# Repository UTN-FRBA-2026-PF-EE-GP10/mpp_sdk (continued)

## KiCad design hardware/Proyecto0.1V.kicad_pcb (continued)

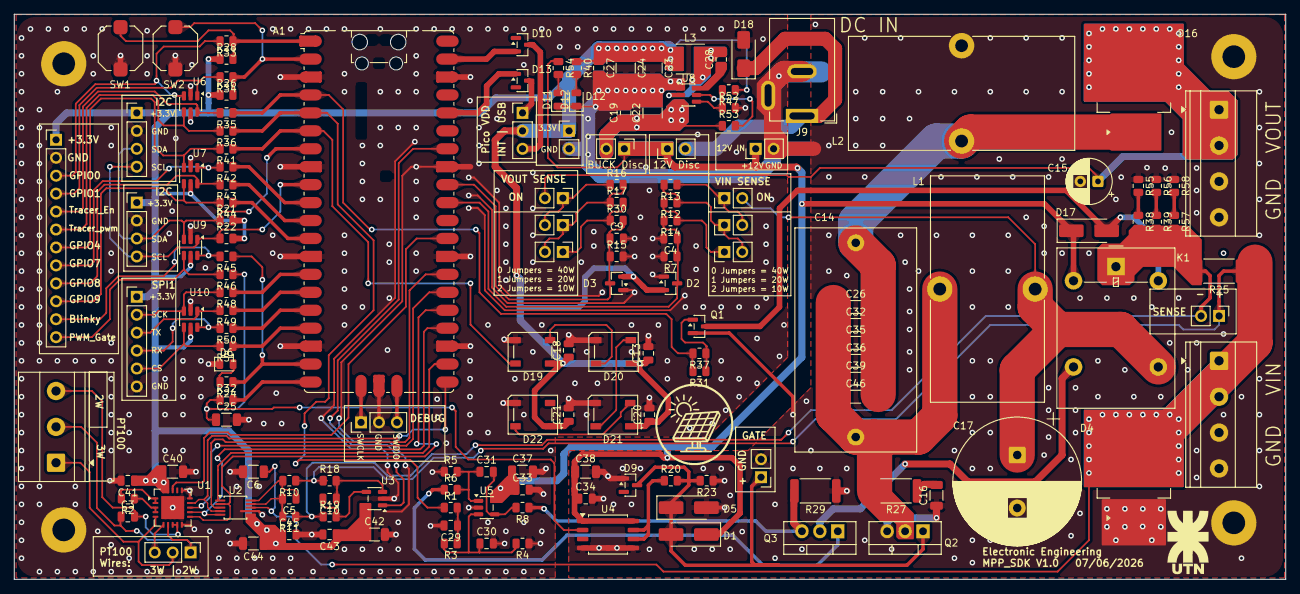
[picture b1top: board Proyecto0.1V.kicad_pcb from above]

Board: 2 copper layers, 180.0 x 80.0 mm, 166 parts (1 on the bottom side), 102 nets.

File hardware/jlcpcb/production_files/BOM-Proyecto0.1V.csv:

Comment,Designator,Footprint,LCSC,Quantity
1TS009A-1800-5000-CT,"SW1,SW2",SW_Push_1TS009xxxx-xxxx-xxxx_6x6x5mm,C319409,2
AP62250WU-7,U8,TSOT-23-6,C5184228,1
BAT54SLT1G,"D10,D13,D2,D3",SOT-23,C19726,4
BZX84C15LT1G,D9,SOT-23,C80857,1
INA229AIDGSR,U2,TSSOP-10_3x3mm_P0.5mm,C2846803,1
INA281A3IDBVR,U3,SOT-23-5,C1517407,1
MAX31865xTP,U1,TQFN-20-1EP_5x5mm_P0.65mm_EP3.25x3.25mm,C118474,1
MBRB20200CT,"D16,D4",TO-263-2,C3874012,2
MMBT3904LT1G,Q1,SOT-23,C81464,1
OPA171AIDBVR,U5,SOT-23-5,C88036,1
SMAJ14A,D18,D_SMA,C99286,1
SRV05-4,"U10,U6,U7,U9",SOT-23-6,C1975211,4
TC4422ESM,U4,SOIC-8_5.3x5.3mm_P1.27mm,C638566,1
XFL4020-222MEC,L3,L_Wurth_WE-LQSH-4020,C122469,1
10R 1% 0805,R18,R_0805_2012Metric,,1
330R 1% 0805,R24,R_0805_2012Metric,,1
330R 1% 0805,R40,R_0805_2012Metric,,1
100nF 10% 50V X7R 0805,C5,C_0805_2012Metric,,1
100nF 10% 50V X7R 0805,C10,C_0805_2012Metric,,1
33R 1% 0805,R20,R_0805_2012Metric,,1
10K 1% 0805,R23,R_0805_2012Metric,,1
YLED0805 Red,D6,LED_0805_2012Metric,,1
SS110,D5,D_SMA_Handsoldering,,1
10R 1% 0805,R10,R_0805_2012Metric,,1
4.7K 1% 0805,R22,R_0805_2012Metric,,1
75K 1% 0805,R17,R_0805_2012Metric,,1
1uF 10% 100V X7R 1206,C40,C_1206_3216Metric,,1
100nF 10% 50V X7R 0805,C27,C_0805_2012Metric,,1
1nF 10% 1KV X7R 1206,C25,C_1206_3216Metric,,1
100K 1% 0805,R53,R_0805_2012Metric,,1
10K 1% 0805,R15,R_0805_2012Metric,,1
1uF 10% 100V X7R 1206,C42,C_1206_3216Metric,,1
10K 1% 0805,R1,R_0805_2012Metric,,1
22uF 10% 25V X7R 1210,C23,C_1210_3225Metric,,1
1uF 10% 100V X7R 1206,C44,C_1206_3216Metric,,1
100nF 10% 50V X7R 0805,C3,C_0805_2012Metric,,1
1uF 10% 100V X7R 1206,C37,C_1206_3216Metric,,1
33R 1% 0805,R47,R_0805_2012Metric,,1
100nF 10% 50V X7R 0805,C19,C_0805_2012Metric,,1
100m 3W 1% 2512,R29,R_2512_6332Metric,,1
10K 1% 0805,R8,R_0805_2012Metric,,1
330R 1% 0805,R42,R_0805_2012Metric,,1
4.7K 1% 0805,R31,R_0805_2012Metric,,1
10R 1% 0805,R19,R_0805_2012Metric,,1
100nF 10% 50V X7R 0805,C9,C_0805_2012Metric,,1
YLED0805 Red,D11,LED_0805_2012Metric,,1
100nF 10% 50V X7R 0805,C43,C_0805_2012Metric,,1
33R 1% 0805,R49,R_0805_2012Metric,,1
100nF 10% 50V X7R 0805,C21,C_0805_2012Metric,,1
10R 1% 0805,R11,R_0805_2012Metric,,1
33R 1% 0805,R50,R_0805_2012Metric,,1
33R 1% 0805,R32,R_0805_2012Metric,,1
4.7K 1% 0805,R28,R_0805_2012Metric,,1
330R 1% 0805,R33,R_0805_2012Metric,,1
SS110,D1,D_SMA_Handsoldering,,1
100nF 10% 50V X7R 0805,C18,C_0805_2012Metric,,1
YLED0805 Red,D12,LED_0805_2012Metric,,1
100nF 10% 50V X7R 0805,C20,C_0805_2012Metric,,1
100nF 10% 50V X7R 0805,C28,C_0805_2012Metric,,1
100nF 10% 50V X7R 0805,C45,C_0805_2012Metric,,1
400R 0.1% 0805,R2,R_0805_2012Metric,,1
4.7K 1% 0805,R21,R_0805_2012Metric,,1
1nF 10% 1KV X7R 1206,C16,C_1206_3216Metric,,1
100nF 10% 50V X7R 0805,C41,C_0805_2012Metric,,1
10K 1% 0805,R5,R_0805_2012Metric,,1
4.7R 3W 1% 2512,R27,R_2512_6332Metric,,1
75K 1% 0805,R30,R_0805_2012Metric,,1
33R 1% 0805,R51,R_0805_2012Metric,,1
100nF 10% 50V X7R 0805,C33,C_0805_2012Metric,,1
75K 1% 0805,R16,R_0805_2012Metric,,1
330R 1% 0805,R41,R_0805_2012Metric,,1
330R 1% 0805,R36,R_0805_2012Metric,,1
1uF 10% 100V X7R 1206,C38,C_1206_3216Metric,,1
330R 1% 0805,R45,R_0805_2012Metric,,1
1uF 10% 100V X7R 1206,C6,C_1206_3216Metric,,1
100nF 10% 50V X7R 0805,C30,C_0805_2012Metric,,1
100nF 10% 50V X7R 0805,C13,C_0805_2012Metric,,1
330R 1% 0805,R46,R_0805_2012Metric,,1
330R 1% 0805,R44,R_0805_2012Metric,,1
75K 1% 0805,R14,R_0805_2012Metric,,1
10m 3W 1% 2512,R25,R_2512_6332Metric,,1
10K 1% 0805,R7,R_0805_2012Metric,,1
75K 1% 0805,R13,R_0805_2012Metric,,1
4.7K 1% 0805,R52,R_0805_2012Metric,,1
33R 1% 0805,R48,R_0805_2012Metric,,1
4.7K 1% 0805,R26,R_0805_2012Metric,,1
4.7K 1% 0805,R37,R_0805_2012Metric,,1
100R 1% 0805,R6,R_0805_2012Metric,,1
2.7K 1% 0805,R4,R_0805_2012Metric,,1
10K 1% 0805,R3,R_0805_2012Metric,,1
100nF 10% 50V X7R 0805,C29,C_0805_2012Metric,,1
4.7K 1% 0805,R54,R_0805_2012Metric,,1
22uF 10% 25V X7R 1210,C24,C_1210_3225Metric,,1
SS110,D17,D_SMA_Handsoldering,,1
22uF 10% 25V X7R 1210,C22,C_1210_3225Metric,,1
100nF 10% 50V X7R 0805,C34,C_0805_2012Metric,,1
330R 1% 0805,R34,R_0805_2012Metric,,1
100nF 10% 50V X7R 0805,C4,C_0805_2012Metric,,1
330R 1% 0805,R35,R_0805_2012Metric,,1
75K 1% 0805,R12,R_0805_2012Metric,,1
100nF 10% 50V X7R 0805,C31,C_0805_2012Metric,,1
330R 1% 0805,R43,R_0805_2012Metric,,1
2.2uF 100V 1206,C32,C_1206_3216Metric,,1
10K 1% 0805,R57,R_0805_2012Metric,,1
2.2uF 100V 1206,C39,C_1206_3216Metric,,1
10K 1% 0805,R56,R_0805_2012Metric,,1
2.2uF 100V 1206,C46,C_1206_3216Metric,,1
10K 1% 0805,R39,R_0805_2012Metric,,1
2.2uF 100V 1206,C36,C_1206_3216Metric,,1
2.2uF 100V 1206,C26,C_1206_3216Metric,,1
10K 1% 0805,R58,R_0805_2012Metric,,1
10K 1% 0805,R38,R_0805_2012Metric,,1
2.2uF 100V 1206,C35,C_1206_3216Metric,,1
10K 1% 0805,R55,R_0805_2012Metric,,1

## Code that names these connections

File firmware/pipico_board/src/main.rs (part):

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// stall the controller the first time that happens.
pub static ADC_SAMPLE_COUNT: AtomicU32 = AtomicU32::new(0);
// True for the duration of a curve-tracer sweep (mode_curve_tracer.rs).
// Neither FirmwareMode may drive the gate while a sweep is stepping the
// bleed PWM - see the override in main()'s loop below. This does not by
// itself mean the panel is back on the SEPIC path once it clears - see
// RELAY_ENGAGED for that.
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    }
}

/// Drives the 4-LED WS2812 strip on GPIO4:
/// - LED 0: Vin (ADC_PWR)
/// - LED 1: Vout (ADC_VOUT)
/// - LED 2: I (ADC_Input_Curr)
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        );
    }

    // SEPIC gate PWM on GPIO15 (PWM_Gate net, through a 10R + 3.3nF network
    // into the driver stage): 100 kHz at the default 125 MHz sysclk with
    // divider 1, top = 1249. Duty is commanded via `DUTY` (u16, 0 = 0 %,
    // 65535 = 100 %) over the Pi SPI link.
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    // Curve-tracer relay + bleed PWM (mode_curve_tracer.rs owns both from
    // here on): idle low/0 is both the safe default and normal MPPT
    // operation (relay released, SEPIC path active, bleed PWM off).
    // Tracer_pwm on GPIO3 -> PWM_SLICE1 channel B (floor(3/2) = 1, odd ->
    // B - same RP2040 fixed GPIO-to-PWM-slice mapping as the SEPIC gate's
    // GPIO15 -> PWM_SLICE7 channel B, datasheet section 4.5.2).
    let mut tracer_pwm_cfg = PwmConfig::default();
    tracer_pwm_cfg.top = mode_curve_tracer::TRACER_PWM_MAX;
    tracer_pwm_cfg.compare_b = 0;
    let tracer_pwm = Pwm::new_output_b(p.PWM_SLICE1, p.PIN_3, tracer_pwm_cfg.clone());
    let tracer_en = Output::new(p.PIN_2, Level::Low);
    // But1 (active-low, switch to GND): edge-triggered sweep start, see
    // mode_curve_tracer::curve_tracer_task.
    let but1 = Input::new(p.PIN_0, Pull::Up);
    let curve_tracer =
        mode_curve_tracer::CurveTracer::new(tracer_en, tracer_pwm, tracer_pwm_cfg, but1);

    // Heartbeat LED (GPIO14, "Blinky" net): toggles in the main loop so a
    // stuck/hung firmware shows as a frozen LED, not just an always-on one.
    let mut heartbeat = Output::new(p.PIN_14, Level::Low);

    let (sm, sm_origin) = spi_slave_pio::init(p.PIO0, p.PIN_10, p.PIN_11, p.PIN_12, p.PIN_13);
    let dma_ch = dma::Channel::new(p.DMA_CH0, DmaIrqs);

    // SPI0 bus: SCK GPIO18, MOSI GPIO19, MISO GPIO16. Chip selects are
    // manual GPIO outputs (not the peripheral's hardware CS) so the bus
    // can be shared with the MAX31865 later; declared here at `main`'s top
    // level so they're never dropped (drop would float the pin).
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    spi_cfg.polarity = Polarity::IdleLow;
    spi_cfg.phase = Phase::CaptureOnSecondTransition;
    let spi = Spi::new_blocking(p.SPI0, p.PIN_18, p.PIN_19, p.PIN_16, spi_cfg);
    let cs_ina = Output::new(p.PIN_17, Level::High);
    let cs_tp100 = Output::new(p.PIN_20, Level::High);
    spawner.spawn(sensors_task(spi, cs_ina, cs_tp100).unwrap());

    let adc = Adc::new_blocking(p.ADC, AdcConfig::default());
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
    spawner.spawn(spi_slave_pio::spi_pio_task(sm, sm_origin, dma_ch).unwrap());

    // GPIO4 NeoPixel packet heartbeat: separate PIO block/DMA channel from
    // the SPI slave above, see neopixel_task's doc comment for why.
    let Pio {
        common: mut pio1_common,
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
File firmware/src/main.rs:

#![no_std]
#![no_main]

use embassy_executor::Spawner;
use embassy_rp::pac;
use embassy_rp::pwm::{Config as PwmConfig, Pwm};
use embassy_time::Timer;
use portable_atomic::{AtomicU16, Ordering};
use {defmt_rtt as _, panic_probe as _};

// ── Shared state (written by SPI/ADC tasks, read by main) ────────────────────
static DUTY: AtomicU16 = AtomicU16::new(0x8000); // 50 % initial
static SIM_V: AtomicU16 = AtomicU16::new(2048);
static SIM_I: AtomicU16 = AtomicU16::new(512);

// ── Pseudo-random (LCG) for simulated ADC readings ───────────────────────────
fn lcg(s: &mut u32) -> u16 {
    *s = s.wrapping_mul(1_664_525).wrapping_add(1_013_904_223);
    ((*s >> 20) & 0xFFF) as u16
}

// ── SPI1 slave — hardware setup ───────────────────────────────────────────────
//
// Protocol (6-byte frame, full-duplex):
//   MOSI (RPi → Pico):  [ DUTY_H | DUTY_L | 0x00 | 0x00 | 0x00 | 0x00 ]
//   MISO (Pico → RPi):  [ 0x00   | 0x00   | V_H  | V_L  | I_H  | I_L  ]
//
// Pins: GPIO10 SCK | GPIO11 TX/MISO | GPIO12 RX/MOSI | GPIO13 CSn
fn spi1_init_slave() {
    // Bring SPI1 out of reset
    pac::RESETS.reset().modify(|w| w.set_spi1(true));
    pac::RESETS.reset().modify(|w| w.set_spi1(false));
    while !pac::RESETS.reset_done().read().spi1() {}

    // 8-bit Motorola SPI mode 0 (CPOL=0, CPHA=0)
    pac::SPI1.cr0().write(|w| {
        w.set_dss(7); // 8-bit
        w.set_frf(0); // Motorola frame format
        w.set_spo(false);
        w.set_sph(false);
        w.set_scr(0);
    });

    // Enable in slave mode
    pac::SPI1.cr1().write(|w| {
        w.set_ms(true); // slave
        w.set_sse(true);
    });

    // Flush stale RX bytes
    while pac::SPI1.sr().read().rne() {
        let _ = pac::SPI1.dr().read().data();
    }

    // Assign SPI1 function (funcsel=1) to GPIO10-13
    for gpio in [10usize, 11, 12, 13] {
        pac::IO_BANK0.gpio(gpio).ctrl().write(|w| w.set_funcsel(1));
    }
}

// Pre-load the TX FIFO with the response for the next master transaction.
// Must be called before the master asserts CS.
fn spi1_preload_tx(v: u16, i: u16) {
    let frame = [0u8, 0, (v >> 8) as u8, v as u8, (i >> 8) as u8, i as u8];
    for &b in &frame {
        while !pac::SPI1.sr().read().tnf() {} // wait: TX not full
        pac::SPI1.dr().write(|w| w.set_data(b as u16));
    }
}

// ── Tasks ─────────────────────────────────────────────────────────────────────

/// Simulates ADC sampling every 10 ms.
/// Replace body with real `embassy_rp::adc` reads when board is connected.
#[embassy_executor::task]
async fn adc_task() {
    let mut rng: u32 = 0xDEAD_BEEF;
    loop {
        SIM_V.store(2000 + (lcg(&mut rng) & 0xFF), Ordering::Relaxed);
        SIM_I.store(500 + (lcg(&mut rng) & 0x7F), Ordering::Relaxed);
        Timer::after_millis(10).await;
    }
}

/// SPI1 slave — waits for full 6-byte frame, applies received duty cycle,
/// pre-loads next response.
#[embassy_executor::task]
async fn spi_slave_task() {
    spi1_init_slave();
    spi1_preload_tx(SIM_V.load(Ordering::Relaxed), SIM_I.load(Ordering::Relaxed));

    let mut rx = [0u8; 6];
    loop {
        // Receive 6 bytes; yield between polls so other tasks keep running
        for slot in &mut rx {
            loop {
                if pac::SPI1.sr().read().rne() {
                    break;
                }
                embassy_futures::yield_now().await;
            }
            *slot = pac::SPI1.dr().read().data() as u8;
        }

        let duty = ((rx[0] as u16) << 8) | rx[1] as u16;
        DUTY.store(duty, Ordering::Relaxed);

        defmt::info!("SPI rx: duty=0x{:04x}", duty);

        // Pre-load response for the next transaction
        spi1_preload_tx(SIM_V.load(Ordering::Relaxed), SIM_I.load(Ordering::Relaxed));
    }
}

// ── Entry point ───────────────────────────────────────────────────────────────

#[embassy_executor::main]
async fn main(spawner: Spawner) {
    let p = embassy_rp::init(Default::default());

    defmt::info!("mpp-firmware booted");

    // PWM on GPIO25 (onboard LED). Switch to PIN_15 / PWM_SLICE7B when board is ready.
    let mut pwm_cfg = PwmConfig::default();
    pwm_cfg.top = 0xFFFF;
    pwm_cfg.compare_b = 0x8000;
    let mut pwm = Pwm::new_output_b(p.PWM_SLICE4, p.PIN_25, pwm_cfg.clone());

    spawner.spawn(adc_task().unwrap());
    spawner.spawn(spi_slave_task().unwrap());

    loop {
        let duty = DUTY.load(Ordering::Relaxed);
        pwm_cfg.compare_b = duty;
        pwm.set_config(&pwm_cfg);

        defmt::info!(
            "duty=0x{:04x}  V_sim={}  I_sim={}",
            duty,
            SIM_V.load(Ordering::Relaxed),
            SIM_I.load(Ordering::Relaxed),
        );

        Timer::after_millis(100).await;
    }
}
